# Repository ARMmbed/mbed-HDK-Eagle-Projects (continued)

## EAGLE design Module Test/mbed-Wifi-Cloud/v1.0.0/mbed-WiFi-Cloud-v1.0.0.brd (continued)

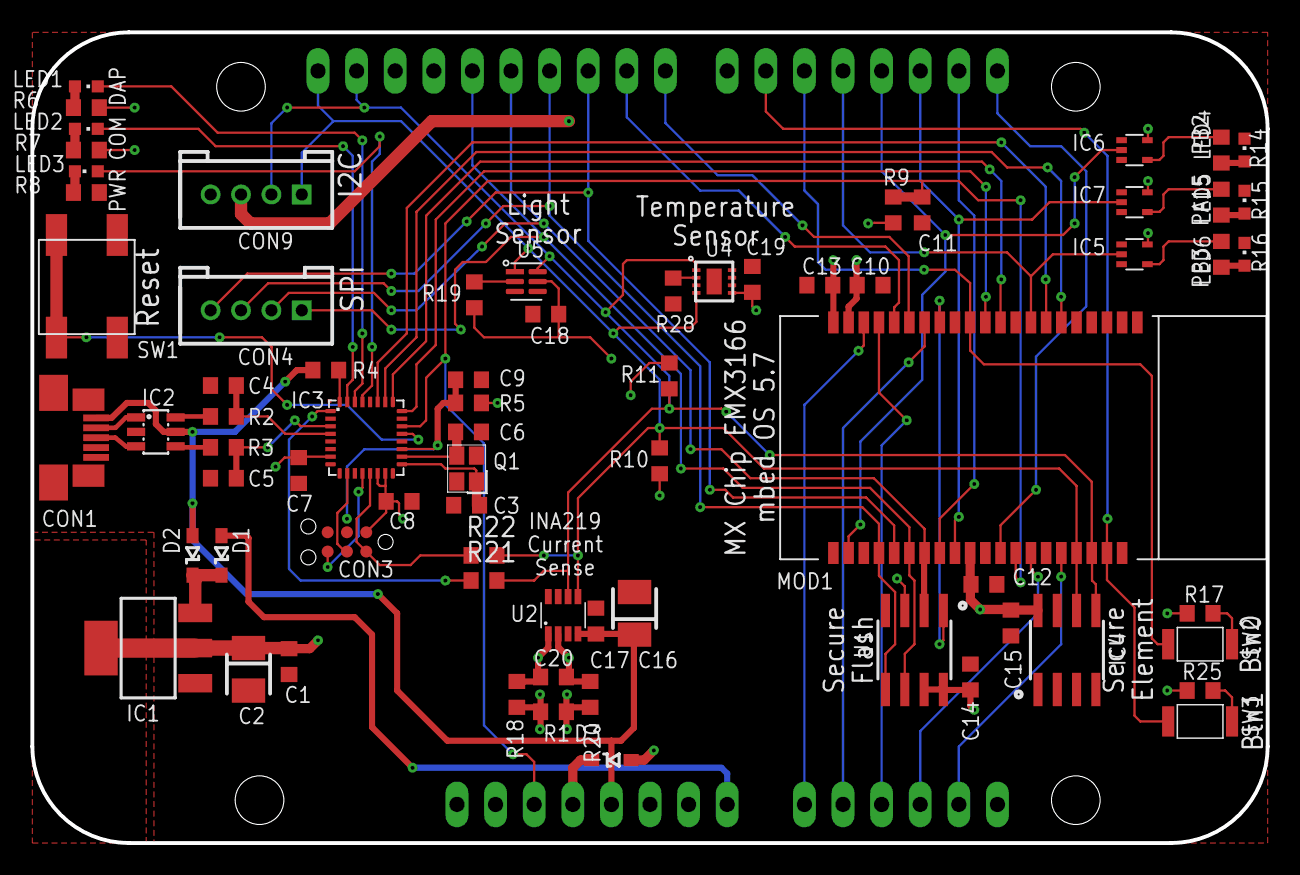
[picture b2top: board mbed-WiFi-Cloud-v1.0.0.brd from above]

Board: 2 copper layers, 81.3 x 53.3 mm, 72 parts (0 on the bottom side), 66 nets.

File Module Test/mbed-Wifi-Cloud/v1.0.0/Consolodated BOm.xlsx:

Qty | Value | Device | Package | Parts | Description | MF | MFN | OC-DIGIKEY | OC-MOUSER | OC-NEWARK | Column1
2 | 0R | R0603 | 0603@1 | R21, R22
14 | 100nF | C0603 | 0603 | C1, C7, C8, C9, C17, C20, C10, C11, C12, C13, C14, C15, C18, C19 | Capacitor
8 | 10k | R0603 | 0603@1 | R5, R9, R18, R20,R17, R19, R25, R28
2 | 10uF | C-POL_B | CASE-B | C2, C16 | Polarised capacitor
2 | 12pF | C0603 | 0603 | C3, C6 | Capacitor
1 | 16MHz | Q_2.5X2.0 | 2.5X2.0 | Q1
1 | 1R@1% | R0603 | 0603@1 | R1
4 | 1k | R0603 | 0603@1 | R7, R8, R14, R15
2 | 22pF | C0603 | 0603 | C4, C5 | Capacitor
2 | 33R | R0603 | 0603@1 | R2, R3
2 | 470R | R0603 | 0603@1 | R6, R16
3 | 4k7 | RESISTOR0603 | 0603 | R4, R10, R11 | Resistor
3 | 74LVC1G125DCK | 74LVC1G125DCK | SC70-5 | IC5, IC6, IC7 | Single Bus Buffer Gate with 3-State Output
1 | ATECC608A | ATECC608A | SO8 | IC4
3 | BAT60A | BAT60A | SOD323 | D1, D2, D3 | SCHOTTKY DIODE | Infineon | BAT60AE6327HTSA1 | BAT60AE6327HTSA1CT-ND | 726-BAT60AE6327 | 85X4127
2 | BLUE | LED0603 | CHIPLED_0603 | LED1, LED6 | SMD LED
1 | EMW3166 | EMW3166 | EMW3166 | MOD1
2 | GREEN | LED0603 | CHIPLED_0603 | LED2, LED4 | SMD LED
1 | GROVE-SPI-PTH | GROVE-SPI-PTH | HW4-2.0 | CON4
1 | GROVE-UART-I2C-PTH | GROVE-UART-I2C-PTH | HW4-2.0 | CON9
1 | IF_MKL26Z128VFM4 | IF_MKL26Z128VFM4 | HVQFN32 | IC3 | CMSIS-DAP Interface (MK20DX128)
1 | INA219AIDCNR | INA219AIDCNR | SOT23-8 | U2 | Current Sense - I2C | Texas Instruments | INA219AIDCNR | 296-23770-1-ND | 595-INA219AIDCNR | 2295989
1 | LD1117S33 | LD1117S33 | SOT223 | IC1 | VOLTAGE REGULATOR SMD 3,3V
1 | MX25R3235FM1IH0 | MX25R3235FM1IH0 | SO8 | U1 | Serial Flash 32 Mb 80 Mhz | Macronix | MX25R3235FM2IH0 | 1092-1174-ND
2 | RED | LED0603 | CHIPLED_0603 | LED3, LED5 | SMD LED
1 | SHT31-DIS-B | SHT31-DIS-B | 8-DFN | U4 | Temperature and Humidity Sensor I2C 2% 8DFN | Sensirion | SHT31-DIS-B | 1649-1011-1-ND | 403-SHT31-DIS-B | 2474218
1 | SKHUALE010 | SKHUALE010 | SKHUALE010 | SW1 | MOMENTARY SWITCH PUSH VERTICAL (4-SPST) | ALPS | SKHUALE010 |  | 688-SKHUALE010
2 | SKRKAEE010 | SKRKAEE010 | SKRKAEE010 | SW2, SW3 | MOMENTARY SWITCH PUSH VERTICAL (SPST) | ALPS | SKRKAEE010 |  | 688-SKRKAE
1 | TC2030-CTX-NL | TC2030-CTX-NL | TC2030-CTX-NL | CON3 | Tag-Connect In Circuit Programming & Debug Cable 6 Pin
1 | TSL25911FN | TSL25911FN | 6-WFDFN | U5 | Sensor Light Digital, High Dynamic Range, 6-WFDFN | ams | TSL25911FN | TSL25911FNCT-ND | 985-TSL25911FN | 09X0688
1 | USBLC6-2SC6 | USBLC6-2SC6 | SOT23-6L | IC2
1 | USB_MICROB | USB_MICROB | MOLEX-47364-0001 | CON1 | USB Connectors

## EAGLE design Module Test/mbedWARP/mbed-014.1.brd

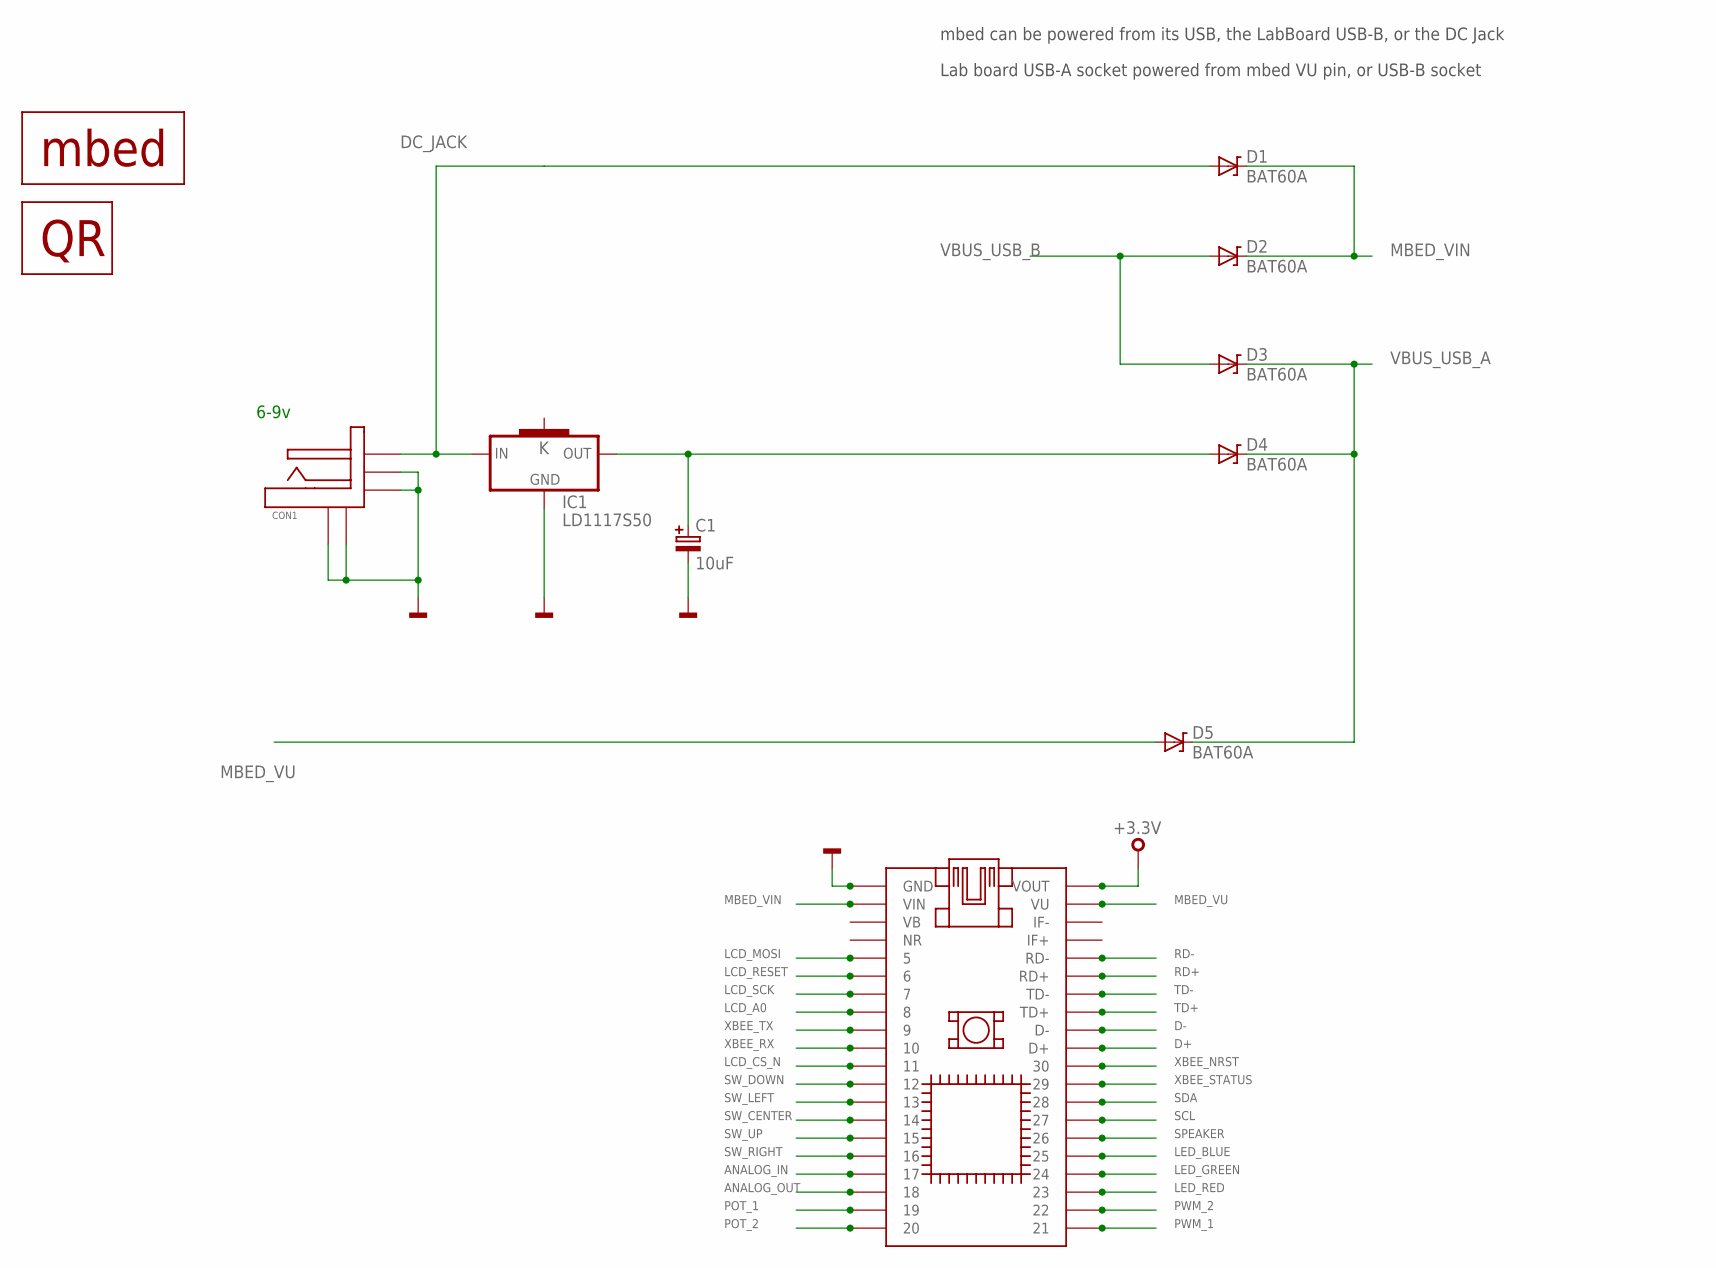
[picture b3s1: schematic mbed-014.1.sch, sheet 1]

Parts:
C1: 10uF; C106B
CON1: FC68145S
D1, D2, D3, D4, D5: BAT60A
IC1: LD1117S50; SOT223
IC2: MBED-SOCKET
QR1: QR-CODE-APP; QR-MBED-APP-BOARD
U$1: MBED-LOGO-BIG

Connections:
+3,3V: IC2.VOUT, IC2.VOUTA; also elsewhere on the board
ANALOG_IN: IC2.17, IC2.17A; also elsewhere on the board
ANALOG_OUT: IC2.18, IC2.18A; also elsewhere on the board
D+: IC2.D+, IC2.D+A; also elsewhere on the board
D-: IC2.D-, IC2.D-A; also elsewhere on the board
DC_JACK: CON1.TIP, D1.A, IC1.3 (IN); also elsewhere on the board
GND: C1.2, CON1.CASE1, CON1.P$5 (CASE2), CON1.SHUNT (SWITCHED), CON1.SLEEVE, IC1.1 (GND), IC2.GND, IC2.GNDA; also elsewhere on the board
LCD_A0: IC2.8, IC2.8A; also elsewhere on the board
LCD_CS_N: IC2.11, IC2.11A; also elsewhere on the board
LCD_MOSI: IC2.5, IC2.5A; also elsewhere on the board
LCD_RESET: IC2.6, IC2.6A; also elsewhere on the board
LCD_SCK: IC2.7, IC2.7A; also elsewhere on the board
LED_BLUE: IC2.25, IC2.25A; also elsewhere on the board
LED_GREEN: IC2.24, IC2.24A; also elsewhere on the board
LED_RED: IC2.23, IC2.23A; also elsewhere on the board
MBED_VIN: D1.K, D2.K, IC2.VIN, IC2.VINA
MBED_VU: D5.A, IC2.VU, IC2.VUA
unnamed: C1.1, D4.A, IC1.2 (OUT)
POT_1: IC2.19, IC2.19A; also elsewhere on the board
POT_2: IC2.20, IC2.20A; also elsewhere on the board
PWM_1: IC2.21, IC2.21A; also elsewhere on the board
PWM_2: IC2.22, IC2.22A; also elsewhere on the board
RD+: IC2.RD+, IC2.RD+A; also elsewhere on the board
RD-: IC2.RD-, IC2.RD-A; also elsewhere on the board
SCL: IC2.27, IC2.27A; also elsewhere on the board
SDA: IC2.28, IC2.28A; also elsewhere on the board
SPEAKER: IC2.26, IC2.26A; also elsewhere on the board
SW_CENTER: IC2.14, IC2.14A; also elsewhere on the board
SW_DOWN: IC2.12, IC2.12A; also elsewhere on the board
SW_LEFT: IC2.13, IC2.13A; also elsewhere on the board
SW_RIGHT: IC2.16, IC2.16A; also elsewhere on the board
SW_UP: IC2.15, IC2.15A; also elsewhere on the board
TD+: IC2.TD+, IC2.TD+A; also elsewhere on the board
TD-: IC2.TD-, IC2.TD-A; also elsewhere on the board
VBUS_USB_A: D3.K, D4.K, D5.K; also elsewhere on the board
VBUS_USB_B: D2.A, D3.A; also elsewhere on the board
XBEE_NRST: IC2.30, IC2.30A; also elsewhere on the board
XBEE_RX: IC2.10, IC2.10A; also elsewhere on the board
XBEE_STATUS: IC2.29, IC2.29A; also elsewhere on the board
XBEE_TX: IC2.9, IC2.9A; also elsewhere on the board

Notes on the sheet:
mbed can be powered from its USB, the LabBoard USB-B, or the DC Jack
Lab board USB-A socket powered from mbed VU pin, or USB-B socket
6-9v

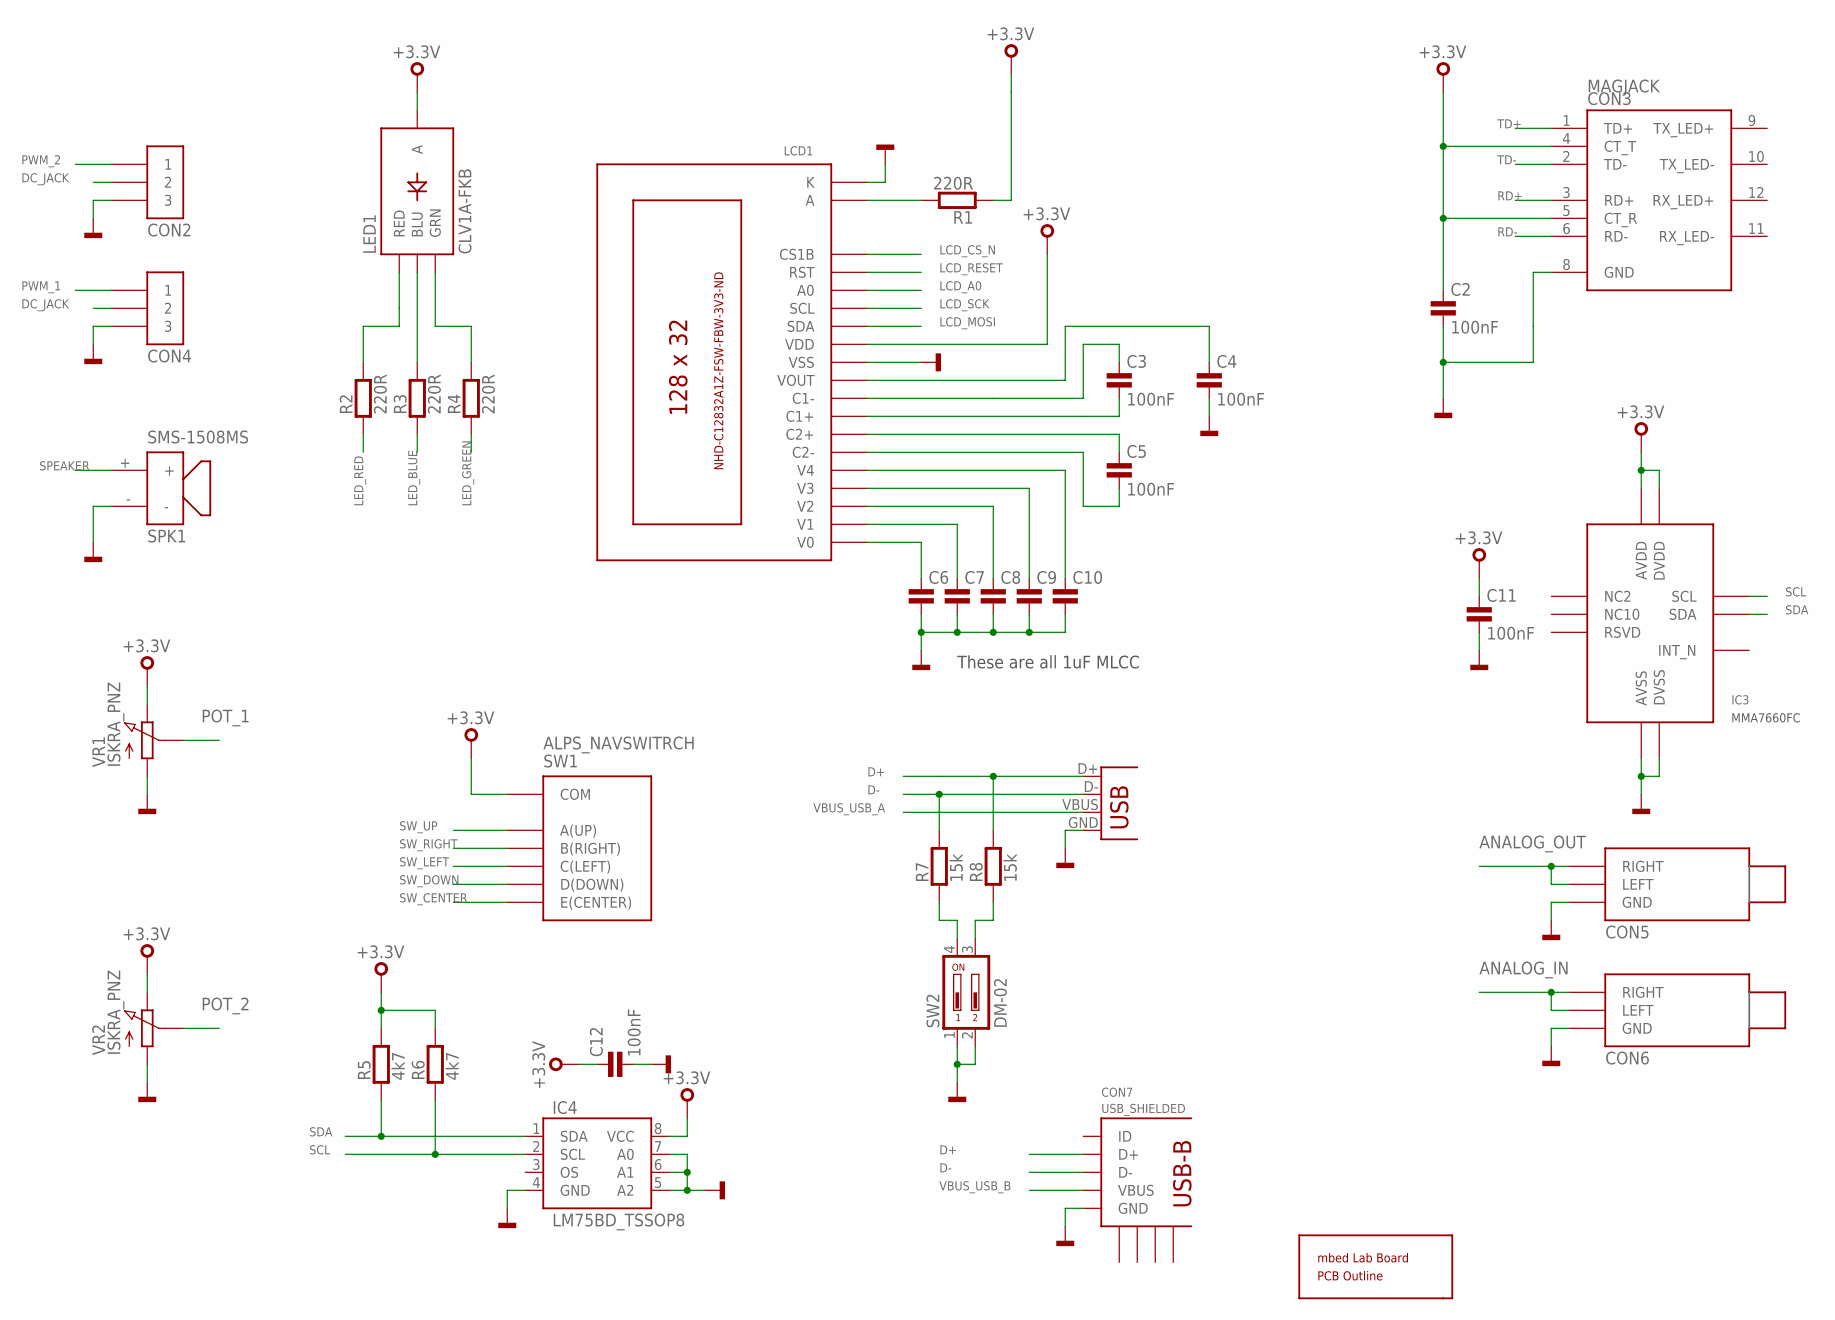
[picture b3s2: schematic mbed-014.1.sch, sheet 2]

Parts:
C2, C3, C4, C5, C6, C7, C8, C9, C10, C11, C12: 100nF; 0402
CON2, CON4: 1X3-HOLES
CON3: MAGJACK
CON5, CON6: 3.5MM_STEREO
CON7: USB_SHIELDED; 5075ABMR-05-SM1
IC3: MMA7660FC; DFN10-3X3MM
IC4: LM75BD_TSSOP8; TSSOP8
LCD1: C12832A1Z
LED1: CLV1A-FKB; PLCC-4
PCB1: LAB_BOARD_OUTLINE
R1, R2, R3, R4: 220R; 0402
R5, R6: 4k7; 0402
R7, R8: 15k; 0402
SPK1: SMS-1508MS; SMS-1508MS-R
SW1: ALPS_NAVSWITRCH; SKRHA_SERIES
SW2: DM-02
VR1, VR2: ISKRA_PNZ; CA14V
X1: USB-A-V

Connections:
+3,3V: C2.1, C11.1, C12.1, CON3.4 (CT_T), CON3.5 (CT_R), IC3.P$3 (AVDD), IC3.P$9 (DVDD), IC4.8 (VCC), LCD1.P$12 (VDD), LED1.2 (A), R1.1, R5.2, R6.2, SW1.P$5 (COM), VR1.P$3 (E), VR2.P$3 (E); also elsewhere on the board
ANALOG_IN: CON6.P$2 (LEFT), CON6.P$3 (RIGHT); also elsewhere on the board
ANALOG_OUT: CON5.P$2 (LEFT), CON5.P$3 (RIGHT); also elsewhere on the board
D+: CON7.D+, R8.2, X1.D+; also elsewhere on the board
D-: CON7.D-, R7.2, X1.D-; also elsewhere on the board
DC_JACK: CON2.P$2 (2), CON4.P$2 (2); also elsewhere on the board
GND: C2.2, C4.2, C6.2, C7.2, C8.2, C9.2, C10.2, C11.2, C12.2, CON2.P$3 (3), CON3.8 (GND), CON4.P$3 (3), CON5.P$1 (GND), CON6.P$1 (GND), CON7.GND, IC3.P$4 (AVSS), IC3.P$8 (DVSS), IC4.4 (GND), IC4.5 (A2), IC4.6 (A1), IC4.7 (A0), LCD1.K, LCD1.P$11 (VSS), SPK1.-, SW2.1, SW2.2, VR1.P$1 (A), VR2.P$1 (A), X1.GND; also elsewhere on the board
LCD_A0: LCD1.P$15 (A0); also elsewhere on the board
LCD_CS_N: LCD1.P$17 (CS1B); also elsewhere on the board
LCD_MOSI: LCD1.P$13 (SDA); also elsewhere on the board
LCD_RESET: LCD1.P$16 (RST); also elsewhere on the board
LCD_SCK: LCD1.P$14 (SCL); also elsewhere on the board
LED_BLUE: R3.1; also elsewhere on the board
LED_GREEN: R4.1; also elsewhere on the board
LED_RED: R2.1; also elsewhere on the board
unnamed: LCD1.A, R1.2
unnamed: R7.1, SW2.4
unnamed: R8.1, SW2.3
unnamed: C3.1, LCD1.P$9 (C1-)
unnamed: C3.2, LCD1.P$8 (C1+)
unnamed: C5.1, LCD1.P$7 (C2+)
unnamed: C5.2, LCD1.P$6 (C2-)
unnamed: C6.1, LCD1.P$1 (V0)
unnamed: C7.1, LCD1.P$2 (V1)
unnamed: C8.1, LCD1.P$3 (V2)
unnamed: C9.1, LCD1.P$4 (V3)
unnamed: C10.1, LCD1.P$5 (V4)
unnamed: LED1.1 (RED), R2.2
unnamed: C4.1, LCD1.P$10 (VOUT)
unnamed: LED1.4 (GRN), R4.2
unnamed: LED1.3 (BLU), R3.2
POT_1: VR1.P$2 (S); also elsewhere on the board
POT_2: VR2.P$2 (S); also elsewhere on the board
PWM_1: CON4.P$1 (1); also elsewhere on the board
PWM_2: CON2.P$1 (1); also elsewhere on the board
RD+: CON3.3 (RD+); also elsewhere on the board
RD-: CON3.6 (RD-); also elsewhere on the board
SCL: IC3.P$6 (SCL), IC4.2 (SCL), R6.1; also elsewhere on the board
SDA: IC3.P$7 (SDA), IC4.1 (SDA), R5.1; also elsewhere on the board
SPEAKER: SPK1.+; also elsewhere on the board
SW_CENTER: SW1.P$2 (E(CENTER)); also elsewhere on the board
SW_DOWN: SW1.P$4 (D(DOWN)); also elsewhere on the board
SW_LEFT: SW1.P$1 (C(LEFT)); also elsewhere on the board
SW_RIGHT: SW1.P$6 (B(RIGHT)); also elsewhere on the board
SW_UP: SW1.P$3 (A(UP)); also elsewhere on the board
TD+: CON3.1 (TD+); also elsewhere on the board
TD-: CON3.2 (TD-); also elsewhere on the board
VBUS_USB_A: X1.VBUS; also elsewhere on the board
VBUS_USB_B: CON7.VBUS; also elsewhere on the board

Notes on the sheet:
These are all 1uF MLCC

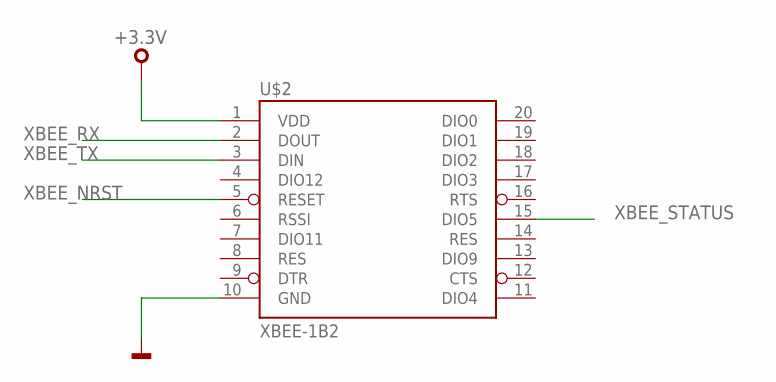
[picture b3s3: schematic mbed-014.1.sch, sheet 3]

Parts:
U$2: XBEE-1B2; XBEE-SILK

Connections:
+3,3V: U$2.1 (VDD); also elsewhere on the board
GND: U$2.10 (GND); also elsewhere on the board
XBEE_NRST: U$2.5 (RESET); also elsewhere on the board
XBEE_RX: U$2.2 (DOUT); also elsewhere on the board
XBEE_STATUS: U$2.15 (DIO5); also elsewhere on the board
XBEE_TX: U$2.3 (DIN); also elsewhere on the board

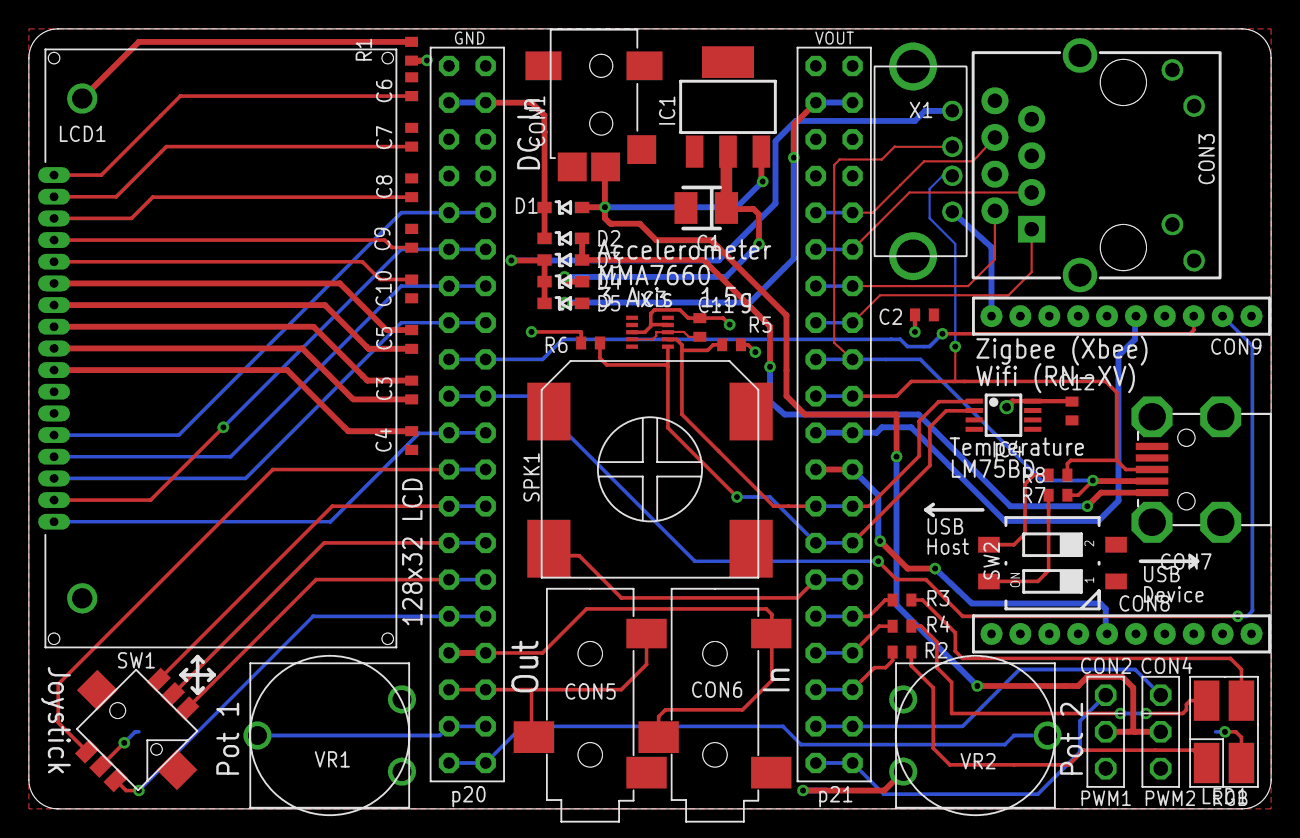
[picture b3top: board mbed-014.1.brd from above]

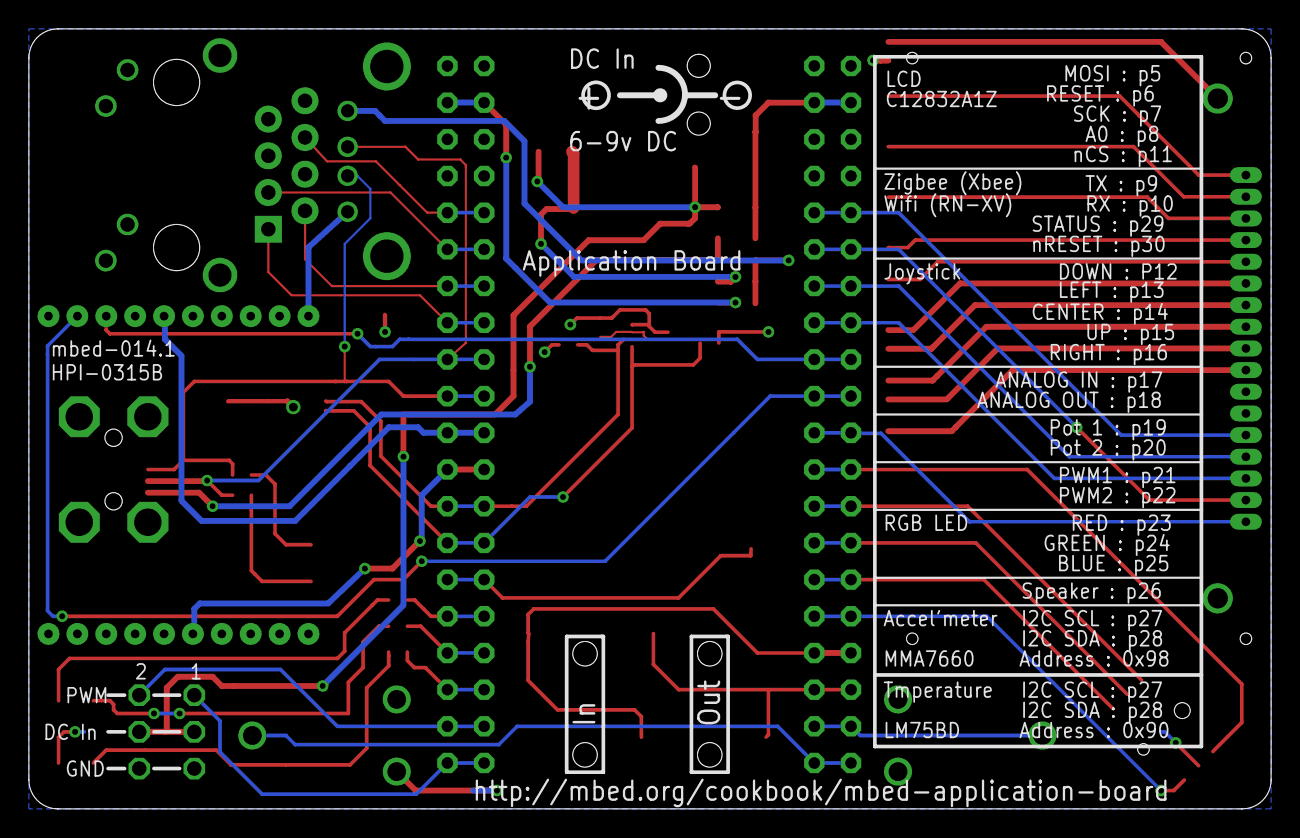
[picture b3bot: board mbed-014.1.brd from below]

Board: 2 copper layers, 86.0 x 54.0 mm, 48 parts (2 on the bottom side), 56 nets.

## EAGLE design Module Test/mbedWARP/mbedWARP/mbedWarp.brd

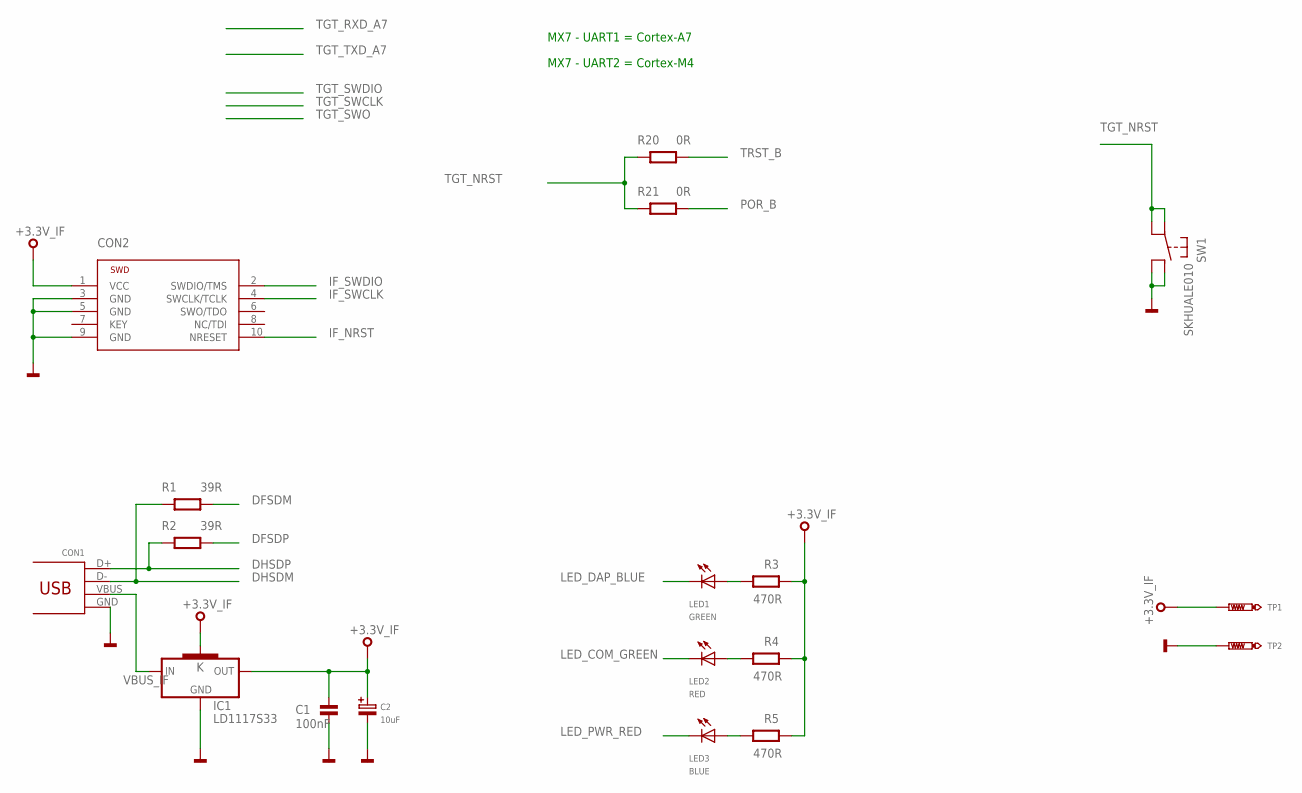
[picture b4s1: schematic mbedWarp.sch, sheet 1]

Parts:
C1: 100nF; 0603
C2: 10uF; CASE-B
CON1: USB_MICROB; MOLEX-47364-0001
CON2: SWD-10-SMD
IC1: LD1117S33; SOT223
LED1: GREEN; CHIPLED_0603
LED2: RED; CHIPLED_0603
LED3: BLUE; CHIPLED_0603
R1, R2: 39R; 0603
R3, R4, R5: 470R; 0603
R20, R21: 0R; 0603
SW1: SKHUALE010
TP1, TP2: TEST-POINT-50R-PTH; TP50-PTH

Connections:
+3.3V_IF: C1.1, C2.1, CON2.1 (VCC), IC1.2 (OUT), IC1.4 (K), R3.1, R4.1, R5.1, TP1.TP; also elsewhere on the board
DFSDM: R1.2; also elsewhere on the board
DFSDP: R2.2; also elsewhere on the board
DHSDM: CON1.D-, R1.1; also elsewhere on the board
DHSDP: CON1.D+, R2.1; also elsewhere on the board
GND: C1.2, C2.2, CON1.GND, CON2.3 (GND), CON2.5 (GND), CON2.9 (GND), IC1.1 (GND), SW1.P$3 (B1), SW1.P$4 (B2), TP2.TP; also elsewhere on the board
IF_NRST: CON2.10 (NRESET); also elsewhere on the board
IF_SWCLK: CON2.4 (SWCLK/TCLK); also elsewhere on the board
IF_SWDIO: CON2.2 (SWDIO/TMS); also elsewhere on the board
LED_COM_GREEN: LED2.C; also elsewhere on the board
LED_DAP_BLUE: LED1.C; also elsewhere on the board
LED_PWR_RED: LED3.C; also elsewhere on the board
unnamed: LED2.A, R4.2
unnamed: LED1.A, R3.2
unnamed: LED3.A, R5.2
POR_B: R21.2; also elsewhere on the board
TGT_NRST: R20.1, R21.1, SW1.P$1 (A1), SW1.P$2 (A2); also elsewhere on the board
TRST_B: R20.2; also elsewhere on the board
VBUS_IF: CON1.VBUS, IC1.3 (IN)

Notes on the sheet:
MX7 - UART1 = Cortex-A7
MX7 - UART2 = Cortex-M4

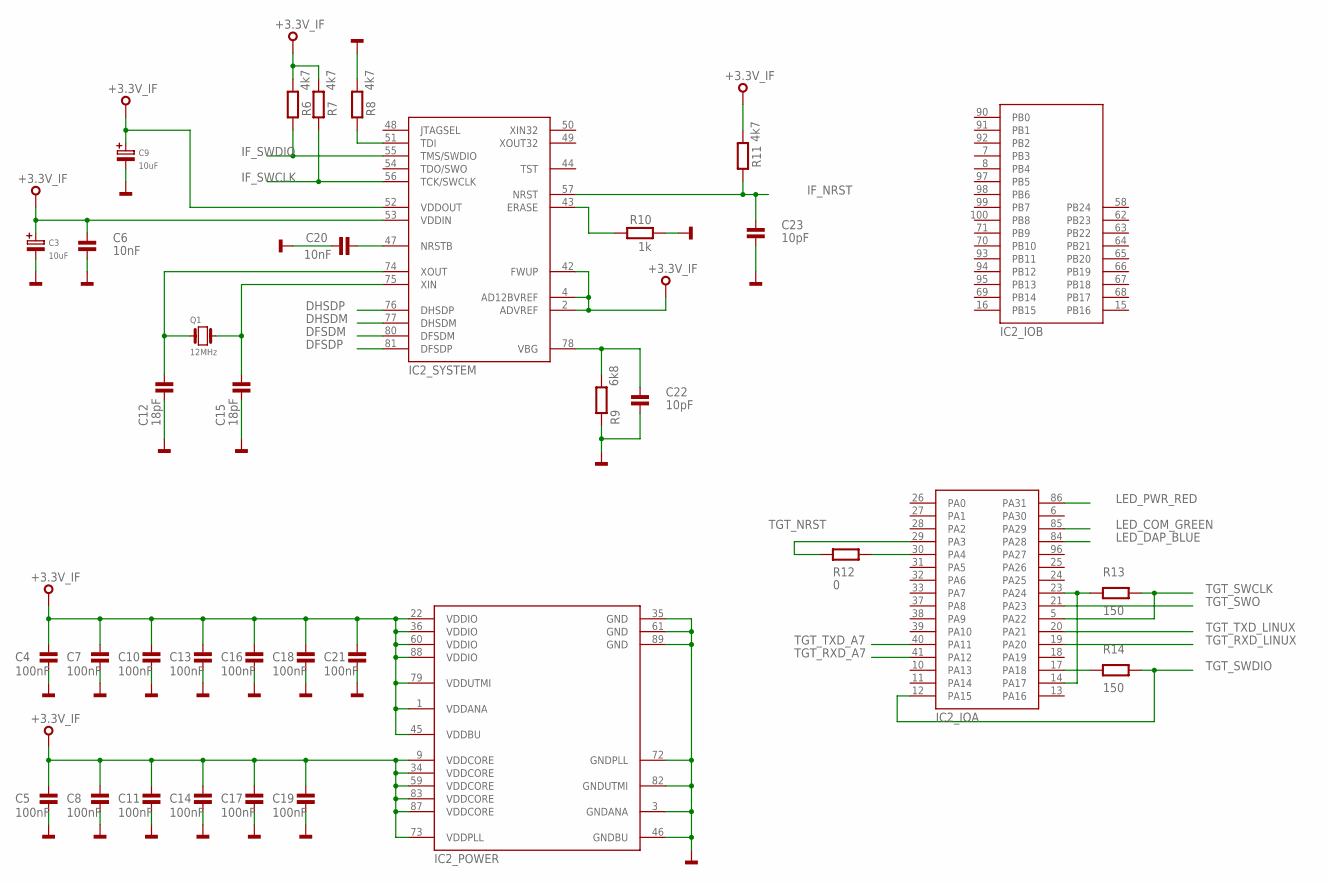
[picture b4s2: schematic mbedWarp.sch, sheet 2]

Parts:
C3, C9: 10uF; CASE-B
C4, C5, C7, C8, C10, C11, C13, C14, C16, C17, C18, C19, C21: 100nF; 0603
C6, C20: 10nF; 0603
C12, C15: 18pF; 0603
C22, C23: 10pF; 0603
IC2: AT91SAM3U2CA; LQFP100
Q1: 12MHz; 3.2X.2.5
R6, R7, R8, R11: 4k7; 0603
R9: 6k8; 0603
R10: 1k; 0603
R12: 0; 0603
R13, R14: 150; 0603

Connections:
+3.3V_IF: C3.1, C4.1, C5.1, C6.1, C7.1, C8.1, C9.1, C10.1, C11.1, C13.1, C14.1, C16.1, C17.1, C18.1, C19.1, C21.1, IC2.1 (VDDANA), IC2.2 (ADVREF), IC2.4 (AD12BVREF), IC2.9 (VDDCORE), IC2.22 (VDDIO), IC2.34 (VDDCORE), IC2.36 (VDDIO), IC2.42 (FWUP), IC2.45 (VDDBU), IC2.52 (VDDOUT), IC2.53 (VDDIN), IC2.59 (VDDCORE), IC2.60 (VDDIO), IC2.73 (VDDPLL), IC2.79 (VDDUTMI), IC2.83 (VDDCORE), IC2.87 (VDDCORE), IC2.88 (VDDIO), R6.2, R7.2, R11.2; also elsewhere on the board
DFSDM: IC2.80 (DFSDM); also elsewhere on the board
DFSDP: IC2.81 (DFSDP); also elsewhere on the board
DHSDM: IC2.77 (DHSDM); also elsewhere on the board
DHSDP: IC2.76 (DHSDP); also elsewhere on the board
GND: C3.2, C4.2, C5.2, C6.2, C7.2, C8.2, C9.2, C10.2, C11.2, C12.2, C13.2, C14.2, C15.2, C16.2, C17.2, C18.2, C19.2, C20.2, C21.2, C22.2, C23.2, IC2.3 (GNDANA), IC2.35 (GND), IC2.46 (GNDBU), IC2.61 (GND), IC2.72 (GNDPLL), IC2.82 (GNDUTMI), IC2.89 (GND), R8.2, R9.1, R10.1; also elsewhere on the board
IF_NRST: C23.1, IC2.57 (NRST), R11.1; also elsewhere on the board
IF_SWCLK: IC2.56 (TCK/SWCLK), R7.1; also elsewhere on the board
IF_SWDIO: IC2.55 (TMS/SWDIO), R6.1; also elsewhere on the board
LED_COM_GREEN: IC2.85 (PA29); also elsewhere on the board
LED_DAP_BLUE: IC2.84 (PA28); also elsewhere on the board
LED_PWR_RED: IC2.86 (PA31); also elsewhere on the board
unnamed: C12.1, IC2.74 (XOUT), Q1.P$1 (1)
unnamed: C15.1, IC2.75 (XIN), Q1.P$3 (2)
unnamed: C20.1, IC2.47 (NRSTB)
unnamed: IC2.51 (TDI), R8.1
unnamed: IC2.43 (ERASE), R10.2
unnamed: C22.1, IC2.78 (VBG), R9.2
unnamed: IC2.14 (PA17), IC2.23 (PA24), R13.1
unnamed: IC2.17 (PA18), R14.1
unnamed: IC2.30 (PA4), R12.2
TGT_NRST: IC2.29 (PA3), R12.1; also elsewhere on the board
TGT_RXD_A7: IC2.41 (PA12); also elsewhere on the board
TGT_RXD_LINUX: IC2.19 (PA20); also elsewhere on the board
TGT_SWCLK: IC2.5 (PA22), R13.2; also elsewhere on the board
TGT_SWDIO: IC2.12 (PA15), R14.2; also elsewhere on the board
TGT_SWO: IC2.21 (PA23); also elsewhere on the board
TGT_TXD_A7: IC2.40 (PA11); also elsewhere on the board
TGT_TXD_LINUX: IC2.20 (PA21); also elsewhere on the board

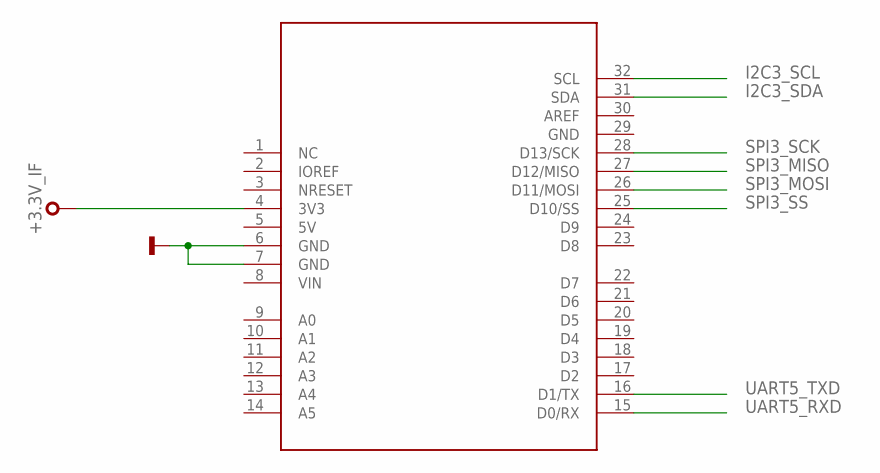
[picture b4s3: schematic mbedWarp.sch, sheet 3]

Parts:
BRD1: ARDUINO-R3_SILK; ARDUINO-R3-SILK

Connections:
+3.3V_IF: BRD1.4 (3V3); also elsewhere on the board
GND: BRD1.6 (GND), BRD1.7 (GND); also elsewhere on the board
I2C3_SCL: BRD1.32 (SCL); also elsewhere on the board
I2C3_SDA: BRD1.31 (SDA); also elsewhere on the board
SPI3_MISO: BRD1.27 (D12/MISO); also elsewhere on the board
SPI3_MOSI: BRD1.26 (D11/MOSI); also elsewhere on the board
SPI3_SCK: BRD1.28 (D13/SCK); also elsewhere on the board
SPI3_SS: BRD1.25 (D10/SS); also elsewhere on the board
UART5_RXD: BRD1.15 (D0/RX); also elsewhere on the board
UART5_TXD: BRD1.16 (D1/TX); also elsewhere on the board

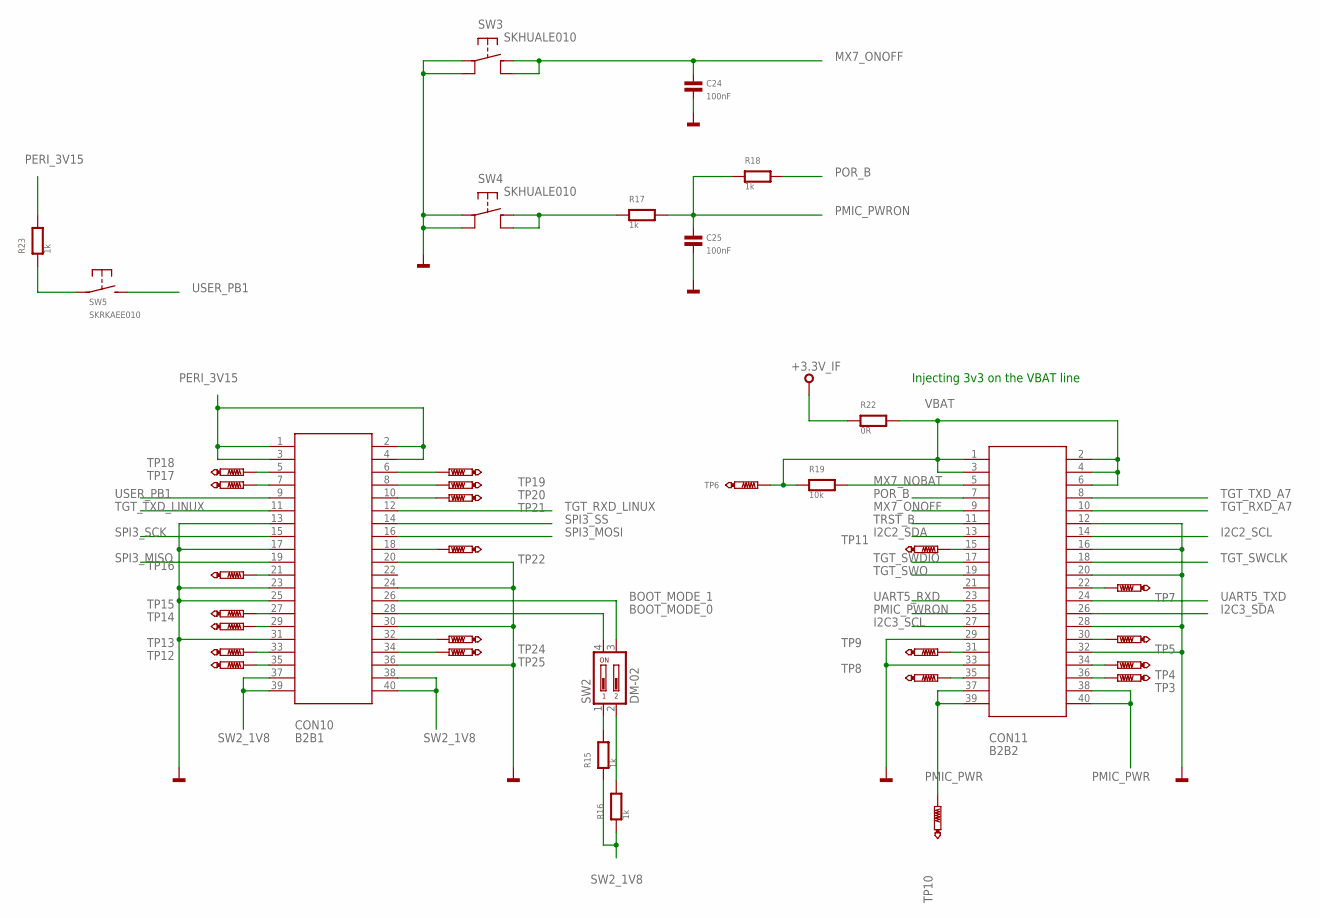
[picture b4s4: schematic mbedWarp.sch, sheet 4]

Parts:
C24, C25: 100nF; 0603
CON10: B2B1; DF40HC-XX-40DS-XX-V
CON11: B2B2; DF40HC-XX-40DS-XX-V
R15, R16, R17, R18, R23: 1k; 0603
R19: 10k; 0603
R22: 0R; 0603
SW2: DM-02
SW3, SW4: SKHUALE010
SW5: SKRKAEE010
TP3, TP4, TP5, TP7, TP8, TP9, TP10, TP11, TP12, TP13, TP14, TP15, TP16, TP17, TP18, TP19, TP20, TP21, TP22, TP24, TP25: PTR1TP06R; TP06R
TP6: TEST-POINT-50R-SMD; TP50-SMD

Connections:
+3.3V_IF: R22.1; also elsewhere on the board
BOOT_MODE_0: CON10.28, SW2.4
BOOT_MODE_1: CON10.26, SW2.3
GND: C24.2, C25.2, CON10.13, CON10.17, CON10.20, CON10.23, CON10.24, CON10.25, CON10.30, CON10.31, CON10.36, CON11.12, CON11.16, CON11.20, CON11.28, CON11.29, CON11.32, CON11.33, SW3.P$1 (A1), SW3.P$2 (A2), SW4.P$1 (A1), SW4.P$2 (A2); also elsewhere on the board
I2C2_SCL: CON11.14
I2C2_SDA: CON11.13
I2C3_SCL: CON11.27; also elsewhere on the board
I2C3_SDA: CON11.26; also elsewhere on the board
MX7_NOBAT: CON11.5, R19.2
MX7_ONOFF: C24.1, CON11.9, SW3.P$3 (B1), SW3.P$4 (B2)
unnamed: R17.1, SW4.P$3 (B1), SW4.P$4 (B2)
unnamed: R23.1, SW5.P$1
unnamed: CON11.36, TP3.TP
unnamed: CON11.22, TP7.TP
unnamed: CON11.30, TP5.TP
unnamed: CON11.34, TP4.TP
unnamed: CON11.15, TP11.TP
unnamed: R15.2, SW2.1
unnamed: R16.2, SW2.2
unnamed: CON11.31, TP9.TP
unnamed: CON11.35, TP8.TP
unnamed: CON10.5, TP18.TP
unnamed: CON10.7, TP17.TP
unnamed: CON10.21, TP16.TP
unnamed: CON10.27, TP15.TP
unnamed: CON10.29, TP14.TP
unnamed: CON10.33, TP13.TP
unnamed: CON10.35, TP12.TP
unnamed: CON10.34, TP25.TP
unnamed: CON10.32, TP24.TP
unnamed: CON10.18, TP22.TP
unnamed: CON10.10, TP21.TP
unnamed: CON10.8, TP20.TP
unnamed: CON10.6, TP19.TP
PERI_3V15: CON10.1, CON10.2, CON10.3, CON10.4, R23.2
PMIC_PWR: CON11.37, CON11.38, CON11.39, CON11.40, TP10.TP
PMIC_PWRON: C25.1, CON11.25, R17.2, R18.1
POR_B: CON11.7, R18.2; also elsewhere on the board
SPI3_MISO: CON10.19; also elsewhere on the board
SPI3_MOSI: CON10.16; also elsewhere on the board
SPI3_SCK: CON10.15; also elsewhere on the board
SPI3_SS: CON10.14; also elsewhere on the board
SW2_1V8: CON10.37, CON10.38, CON10.39, CON10.40, R15.1, R16.1
TGT_RXD_A7: CON11.10; also elsewhere on the board
TGT_RXD_LINUX: CON10.12; also elsewhere on the board
TGT_SWCLK: CON11.18; also elsewhere on the board
TGT_SWDIO: CON11.17; also elsewhere on the board
TGT_SWO: CON11.19; also elsewhere on the board
TGT_TXD_A7: CON11.8; also elsewhere on the board
TGT_TXD_LINUX: CON10.11; also elsewhere on the board
TRST_B: CON11.11; also elsewhere on the board
UART5_RXD: CON11.23; also elsewhere on the board
UART5_TXD: CON11.24; also elsewhere on the board
USER_PB1: CON10.9, SW5.P$2 (S)
VBAT: CON11.1, CON11.2, CON11.3, CON11.4, CON11.6, R19.1, R22.2, TP6.TP

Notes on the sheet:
Injecting 3v3 on the VBAT line
